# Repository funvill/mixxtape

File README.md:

# Mixxtape — a cassette you can actually record on

A 2-layer PCB in the form factor of a compact cassette (99.5 × 63.5 mm)
that slides into a real Norelco cassette case. The bare board **is** the object —
no enclosure, no bezel.

An onboard MEMS microphone records three 4-minute tracks. Hold REC to record,
release to stop. Pair it to any Bluetooth earbuds or speaker and press PLAY.

Cassette-shaped Bluetooth *players* exist. Nobody ships a cassette-shaped
**recorder** — and recording is the part that made a mixtape a mixtape.

![The Mixxtape board turning, front and back. The front carries the ESP32, two
rings of RGB LEDs around the routed-out reel windows, four buttons and a USB-C
port; the back is covered edge to edge in a peony line-art silkscreen.](artwork/mixxtape.gif)

<sub>3D render from KiCad. The mask reads green here because that is the
viewer's default — the board ships **matte white**, which is what makes the
sharpie label work.</sub>

![A cassette and its paper insert, both carrying the same black peony line-art
on an off-white ground, the insert showing a blank ruled label
box.](artwork/case-mockup.png)

<sub>Artwork mockup of the B-side design and the J-card insert. The board is
the object; this shows where the artwork is going.</sub>

## How you use it

- **Hold REC** — records. Release stops. Recording always overwrites the current
  track from zero — recording *is* erasing, same as tape.
- **PLAY** — plays all three tracks in order. It's a tape side, not three voice
  memos.
- **TRACK** — cycles track 1 → 2 → 3.
- **MODE (hold 2 s)** — pairing. Hold the board against your speaker; it picks
  the closest device by signal strength. No phone, no app, no list.
- Plug it in and it auto-reconnects to the last thing it paired with.

## Notable design features

- **Snap-off write-protect tab.** A mouse-bitten break-off PCB tab carries a
  trace to a GPIO. Snap it and the firmware refuses to record — permanently.
  Handing someone a tape becomes a ritual with a physical, irreversible step.
- **The reels show tape position.** Twelve RGB LEDs ring each routed-out reel
  window. During playback the left ring empties and the right ring fills, like
  tape transferring between reels. Red pulse tracks recording level.
- **Matte white solder mask** so you can sharpie the label on, with a ruled
  label block silkscreened where a cassette's paper label sits.
- **No battery.** USB-C only, and there is no charging circuit on the board
  at all. A cassette's promise is that you find it years later and it still
  works.
- **Jig-programmed.** No USB-UART on the board — USB-C is power only.
  Firmware loads through six pogo-pin pads via a programming jig.

## Hardware summary

Every fitted part is stocked at JLCPCB. The project rule is a minimum of 5,000
in stock, so a run never stalls on one line item — with a single documented
exception: **the microphone sits at ~3,500**, because no digital MEMS
microphone at JLCPCB clears the bar, and the one that does is analogue and
would wreck the audio path.

| Block | Part | JLCPCB | Qty | Notes |
|---|---|---|---|---|
| MCU | ESP32-WROOM-32E-N4 | [C701341](https://jlcpcb.com/partdetail/C701341) | 1 | The original Xtensa ESP32 — the only one with Classic Bluetooth, so the only one that can be an A2DP *source* |
| Microphone | MSM261DHT006 | [C51928215](https://jlcpcb.com/partdetail/C51928215) | 1 | **PDM** digital MEMS, mono, **top-ported** — sound enters from the component side, so there is no hole through the board |
| Storage | GD25Q128ESIG | [C2758105](https://jlcpcb.com/partdetail/C2758105) | 1 | 16 MB NOR flash, separate from the module's own flash. Three fixed slots, ~4 min each. Winbond W25Q128JVSIQ ([C97521](https://jlcpcb.com/partdetail/C97521)) is a drop-in second source |
| Indicators | XL-2020RGBC-2812B | [C5349954](https://jlcpcb.com/partdetail/C5349954) | 29 | WS2812-compatible RGB. Two 12-LED reel rings, three track lamps, REC, BT |
| LED data buffer | SN74AHCT1G125 | [C7484](https://jlcpcb.com/partdetail/C7484) | 1 | Lifts the ESP32's 3.3 V data line to the LEDs' 5 V rail |
| Regulator | AMS1117-3.3 | [C6186](https://jlcpcb.com/partdetail/C6186) | 1 | 5 V USB down to 3.3 V |
| USB-C | TYPE-C-31-M-12 | [C165948](https://jlcpcb.com/partdetail/C165948) | 1 | Power and CC sensing only — no data lines |
| Buttons | TS-1187A-B-A-B | [C318884](https://jlcpcb.com/partdetail/C318884) | 4 | REC, PLAY, TRACK, MODE |
| Write-protect tab | — | — | 1 | Not a part. A mouse-bitten PCB tongue carrying a net tie; snap it and recording is disabled for good |
| Programming pads | — | — | 1 | Six bare pogo targets. No USB-UART on the board |

Passives are all JLCPCB basic-library parts:
[10 µF 0805](https://jlcpcb.com/partdetail/C15850) ×2 (rail bulk),
[10 µF 0402](https://jlcpcb.com/partdetail/C15525),
[1 µF](https://jlcpcb.com/partdetail/C52923) (the ESP32's EN delay),
[100 nF](https://jlcpcb.com/partdetail/C1525) ×12,
[10 k](https://jlcpcb.com/partdetail/C25804) ×7,
[5.1 k](https://jlcpcb.com/partdetail/C25905) ×2 (the USB-C CC pull-downs) and
[100 Ω](https://jlcpcb.com/partdetail/C25076) (microphone supply isolation).

| | |
|---|---|
| Audio | 44.1 kHz mono, ADPCM-encoded at record time; playback decodes with table lookups and hands PCM to the Bluetooth stack |
| Power | USB-C only, power and CC sense. No battery, no charger |
| Board | 2-layer, 99.50 × 63.50 mm, matte white solder mask with black silkscreen |
| Cost | **$9.41/board** at a run of 20 — $173.14 in parts plus $15.00 of setup fees for five extended-library parts |

Full detail, with live stock and pricing, is in the
[generated BOM](docs/cassette-recorder-bom-v4.md) — it is derived from the
schematic, so it cannot drift out of step with it.

## Project status

**Design locked, schematic and firmware core underway.** `hardware/` holds a
KiCad 9 project with a first-pass schematic (ERC-clean) and JLCPCB part
libraries. `firmware/` has the ESP-IDF skeleton plus the host-tested core —
crash-safe slot manager, ADPCM codec, playback sequencer, reel display,
pairing policy, bond table and record limiter — all proven without hardware,
since there is no devkit. Target: a prototype run of 3–5 boards, then a full
run of 20. What is left needs a board in hand: the SPI flash, I²S capture,
the A2DP plumbing, LED output, and A2DP against real earbuds.

## Documentation

**Before ordering boards:**

- [Pre-production checklist](docs/PRE-PRODUCTION-CHECKLIST.md) — the
  case-fit test, open decisions, and what to re-quote
- [Case-fit test sheet](docs/case-fit-test-1to1.pdf) — print at 100%, cut
  out, put in a real cassette case

**For people using one:**

- [Cassette insert template](docs/jcard-template-1to1.pdf) — double-sided
  J-card for the case, 1:1, print at 100% ([side 1](docs/jcard-template-side1.svg), [side 2](docs/jcard-template-side2.svg))
- [Documentation index](docs/README.md) — everything below, organised
- [Quick-start pictograms](docs/quick-start-pictograms.html) — wordless
  instructions, one printable sheet
- [Manual](docs/MANUAL.md) — how to record, play, pair, and what the lights mean
- [FAQ](docs/FAQ.md) — including the honest limitations

**For people building or hacking one:**

- [Project write-up](docs/cassette-project-writeup.md) — the pitch, design
  rationale, and open questions
- [Agent handoff brief](docs/cassette-recorder-agent-brief.md) — the
  authoritative spec: locked decisions, GPIO map, behaviour spec, phase order
- [Bill of materials](docs/cassette-recorder-bom-v4.md) — generated from the
  schematic with live JLCPCB prices and stock, so it cannot drift
- [Line-out option](docs/line-out-option.md) — rejected; kept for the reasoning
  and the verified part numbers
- [Prior art](docs/prior-art.md) — research on cassette-form-factor projects
- [Firmware plan](docs/firmware-plan.md) — architecture, milestones, and
  hardware interface for the firmware agent

## Prior art

- **Mixtape Alpha** (Open Music Labs with Jie Qi / MIT Media Lab, 2012) — a
  cassette-shaped ATmega328p synth; the bare-PCB-as-object philosophy comes
  straight from it.
- **Mixxtape** (Mixxim) — the commercial cassette-shaped Bluetooth *player*.
  The thing this project is not.

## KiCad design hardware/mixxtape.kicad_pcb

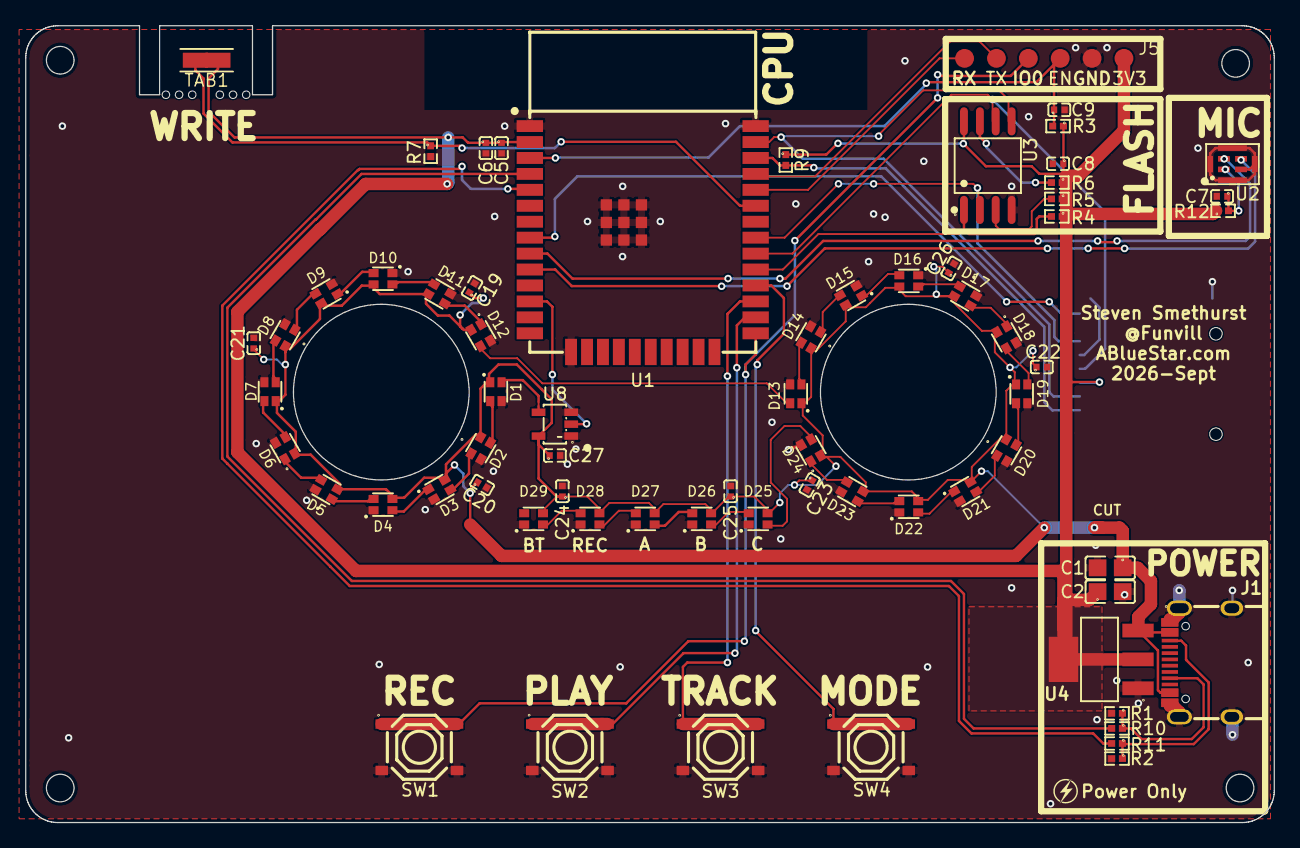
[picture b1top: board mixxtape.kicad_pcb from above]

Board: 2 copper layers, 99.5 x 63.5 mm, 70 parts (1 on the bottom side), 56 nets.

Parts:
C1, C2: 10uF; C0805
C5, C6, C7, C8, C19, C20, C21, C22, C23, C24, C25, C26, C27: C0402
C9: 1uF; C0402
D1, D2, D3, D4, D5, D6, D7, D8, D9, D10, D11, D12, D13, D14, D15, D16, D17, D18, D19, D20, D21, D22, D23, D24, D25, D26, D27, D28, D29: XL-1615RGBC-2812B; LED-SMD_4P-L1.6-W1.5_XL-1615RGBC-2812B
J1: USB-C_SMD-TYPE-C-31-M-12_1
J4: TF-SMD_TF-01A
J5: PROG_JIG; PROG_JIG_6PAD
MB1: MOUSEBITE_6
R1, R2: R0402
R3, R4, R5, R6, R7, R9, R10, R11: R0603; R0402
R12: 100R; R0402
SW1, SW2, SW3, SW4: SW-SMD_4P-L5.1-W5.1-P3.70-LS6.5-TL_H1.5
TAB1: WRITE-PROTECT; TAB_BREAKOFF_LINK
U1: WIFI-SMD_ESP32-WROOM-32E
U2: LGA-8_L4.0-W3.0-R_WMM7040DT0
U3: SOIC-8_L5.3-W5.3-P1.27-LS8.0-BL
U4: SOT-223-3_L6.5-W3.4-P2.30-LS7.0-BR
U8: SOT-23-5_L3.0-W1.7-P0.95-LS2.8-BR

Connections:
3V3: C2.1, C5.1, C6.1, C8.1, J4.4, J5.1, R3.1, R4.1, R5.1, R6.1, R9.1, R12.1, TAB1.1, U1.2, U3.8, U4.2, U4.4
BTN_MODE: SW4.1, SW4.2, U1.28
BTN_PLAY: SW2.1, SW2.2, U1.26
BTN_REC: J5.4, SW1.1, SW1.2, U1.25
BTN_TRACK: SW3.1, SW3.2, U1.27
CC1: J1.A5, R1.1, R10.1
CC1_SENSE: R10.2, U1.4
CC2: J1.B5, R2.1, R11.1
CC2_SENSE: R11.2, U1.5
EN: C9.1, J5.3, R3.2, U1.3
FLASH_HOLD_N: R6.2, U3.7
FLASH_WP_N: R5.2, U3.3
GND: C1.2, C2.2, C5.2, C6.2, C7.2, C8.2, C9.2, C19.2, C20.2, C21.2, C22.2, C23.2, C24.2, C25.2, C26.2, C27.2, D1.1, D2.1, D3.1, D4.1, D5.1, D6.1, D7.1, D8.1, D9.1, D10.1, D11.1, D12.1, D13.1, D14.1, D15.1, D16.1, D17.1, D18.1, D19.1, D20.1, D21.1, D22.1, D23.1, D24.1, D25.1, D26.1, D27.1, D28.1, D29.1, J1.1, J1.2, J1.3, J1.4, J1.A1B12, J1.B1A12, J4.6, J4.10, J4.11, J4.12, J4.13, J5.2, R1.2, R2.2, R7.2, SW1.3, SW1.4, SW2.3, SW2.4, SW3.3, SW3.4, SW4.3, SW4.4, U1.1, U1.15, U1.38, U1.39, U2.2, U2.5, U2.6, U2.7, U2.8, U3.4, U4.1, U8.1, U8.3
LD1: D1.4, D2.2
LD2: D2.4, D3.2
LD3: D3.4, D4.2
LD4: D4.4, D5.2
LD5: D5.4, D6.2
LD6: D6.4, D7.2
LD7: D7.4, D8.2
LD8: D8.4, D9.2
LD9: D9.4, D10.2
LD10: D10.4, D11.2
LD11: D11.4, D12.2
LD12: D12.4, D13.2
LD13: D13.4, D14.2
LD14: D14.4, D15.2
LD15: D15.4, D16.2
LD16: D16.4, D17.2
LD17: D17.4, D18.2
LD18: D18.4, D19.2
LD19: D19.4, D20.2
LD20: D20.4, D21.2
LD21: D21.4, D22.2
LD22: D22.4, D23.2
LD23: D23.4, D24.2
LD24: D24.4, D25.2
LD25: D25.4, D26.2
LD26: D26.4, D27.2
LD27: D27.4, D28.2
LD28: D28.4, D29.2
LED_DATA: U1.12, U8.2
LED_DATA_5V: D1.2, U8.4
MIC_VDD: C7.1, R12.2, U2.1
PDM_CLK: U1.10, U2.3
PDM_DATA: U1.9, U2.4
SD_CS_N: J4.2, R9.2, U1.36
SD_DETECT: J4.9, U1.8
SPI_CLK: J4.5, U1.30, U3.6
SPI_CS_N: R4.2, U1.29, U3.1
SPI_MISO: J4.7, U1.31, U3.2
SPI_MOSI: J4.3, U1.37, U3.5
TAB_SENSE: R7.1, TAB1.2, U1.33
UART_RX: J5.6, U1.34
UART_TX: J5.5, U1.35
VBUS: C1.1, C19.1, C20.1, C21.1, C22.1, C23.1, C24.1, C25.1, C26.1, C27.1, D1.3, D2.3, D3.3, D4.3, D5.3, D6.3, D7.3, D8.3, D9.3, D10.3, D11.3, D12.3, D13.3, D14.3, D15.3, D16.3, D17.3, D18.3, D19.3, D20.3, D21.3, D22.3, D23.3, D24.3, D25.3, D26.3, D27.3, D28.3, D29.3, J1.A4B9, J1.B4A9, U4.3, U8.5

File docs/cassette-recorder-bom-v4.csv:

Comment,Designator,Footprint,JLCPCB Part #
"22uF","C1 C2","C0805","C45783"
"10uF","C5","C0402","C15525"
"100nF","C6 C7 C8 C19 C20 C21 C22 C23 C24 C25 C26 C27","C0402","C1525"
"1uF","C9","C0402","C29266"
"WS2812B-2020","D1 D2 D3 D4 D5 D6 D7 D8 D9 D10 D11 D12 D13 D14 D15 D16 D17 D18 D19 D20 D21 D22 D23 D24 D25 D26 D27 D28 D29","LED-SMD_4P-L2.0-W2.0-TL_WS2812B-2020","C5349955"
"USB-C-16P","J1","USB-C_SMD-TYPE-C-31-M-12_1","C165948"
"5.1k","R1 R2","R0402","C25905"
"10k","R3 R4 R5 R6 R7 R10 R11","R0603","C25804"
"100R","R12","R0402","C25076"
"PLAY / TRACK / MODE / REC","SW1 SW2 SW3 SW4","SW-SMD_4P-L5.1-W5.1-P3.70-LS6.5-TL_H1.5","C318884"
"ESP32-WROOM-32E-N4","U1","WIFI-SMD_ESP32-WROOM-32E","C701341"
"MSM261DHT006","U2","LGA-8_L4.0-W3.0-R_WMM7040DT0","C51928215"
"W25Q128JVSIQ","U3","SOIC-8_L5.3-W5.3-P1.27-LS8.0-BL","C97521"
"AMS1117-3.3","U4","SOT-223-3_L6.5-W3.4-P2.30-LS7.0-BR","C6186"
"SN74AHCT1G125","U8","SOT-23-5_L3.0-W1.7-P0.95-LS2.8-BR","C7484"

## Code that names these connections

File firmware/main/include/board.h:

/* Pin map for the rev 0.1 board.
 *
 * Authoritative source: docs/firmware-plan.md sec.2, which supersedes the
 * GPIO table in docs/cassette-recorder-agent-brief.md sec.5 (USB-C is now
 * power-only, programming is via the J5 pogo pads, and SENSOR_VP/VN sense
 * the USB-C CC lines).
 *
 * ESP32 constraints honoured here:
 *   GPIO 6-11  are the module's own flash — never used
 *   GPIO 12    is the MTDI strap and must be low at boot — left unused
 *   GPIO 34/35/36/39 are input-only
 */
#ifndef BOARD_H
#define BOARD_H

#include "tape_layout.h" /* TAPE_SAMPLE_RATE */

/* --- PDM microphone (MSM261DHT006, mono, L/R tied low) --------------
 * PDM rather than I2S: two wires instead of three, so the old bit-clock
 * pin (GPIO26) is now free. The ESP32's I2S peripheral does PDM receive
 * in hardware, decimating to PCM on the way in, so nothing downstream
 * changes.
 *
 * Clock rate matters here. PDM clock = sample rate x downsample ratio:
 *   44100 x 64  = 2.8224 MHz  -> inside the mic's 1.1-4.8 MHz window
 *   44100 x 128 = 5.6448 MHz  -> ABOVE its 4.8 MHz maximum
 * so the downsample ratio must be 64. Picking 128 would run the part out
 * of spec and is the obvious mistake to make here.
 *
 * The part is TOP-ported: sound enters from the component side, and there
 * is deliberately no hole through the board beneath it. Keep its top face
 * clear of case ribs, labels and fingers.
 */
#define PIN_PDM_CLK  25 /* ESP32 -> mic, 2.8224 MHz */
#define PIN_PDM_DATA 33 /* mic -> ESP32            */

#define PDM_DOWNSAMPLE_RATIO 64
#define PDM_CLOCK_HZ         (TAPE_SAMPLE_RATE * PDM_DOWNSAMPLE_RATIO)

/* --- VSPI: audio flash (W25Q128) + optional microSD (DNP) ----------- */
#define PIN_SPI_SCK   18
#define PIN_SPI_MISO  19
#define PIN_SPI_MOSI  23
#define PIN_FLASH_CS   5
#define PIN_SD_CS     22 /* microSD is DNP on the default build         */
#define PIN_SD_DETECT 32 /* switch to GND; needs an internal pull-up    */

/* --- WS2812 chain (via SN74AHCT1G125 level shifter) ----------------- */
#define PIN_LED_DATA 27
#define LED_COUNT    29
#define LED_REEL_LEFT_FIRST   0  /* D1-D12  */
#define LED_REEL_LEFT_COUNT   12
#define LED_REEL_RIGHT_FIRST  12 /* D13-D24 */
#define LED_REEL_RIGHT_COUNT  12
#define LED_TRACK_FIRST       24 /* D25-D27 */
#define LED_TRACK_COUNT       3
#define LED_REC               27 /* D28 */
#define LED_BT                28 /* D29 */

/* Global brightness ceiling. All 29 LEDs at full white is ~1.7 A; the
 * default USB-C budget is 500 mA until CC sensing says otherwise. */
/* Re-derived 2026-08-30 against the real part. At 5 mA/channel all 29 LEDs
 * at full white draw about 435 mA, not the 1.7 A the old caps assumed.
 *
 *   Default USB (500 mA guaranteed): an ESP32 Bluetooth TX burst takes
 *   ~250 mA through the linear regulator, leaving ~250 mA for the array.
 *   130/255 gives 435 * 130/255 = 222 mA, for ~472 mA total.
 *
 *   A 1.5 A source can supply the whole array at full, so the cap there is
 *   the part's own limit rather than the supply's.
 *
 * Firmware MUST read CC1_SENSE/CC2_SENSE before using the HIGH cap - the
 * board advertises itself as a plain sink (5.1k Rd), so a host is only
 * obliged to give 500 mA. */
#define LED_BRIGHTNESS_USB_DEFAULT 130 /* /255, ~51%, ~222 mA of array */
#define LED_BRIGHTNESS_USB_HIGH    255 /* /255, full, ~435 mA of array  */

/* --- Buttons: active low, internal pull-ups -------------------------- */
#define PIN_BTN_REC   0  /* also the BOOT strap — safe as active-low     */
#define PIN_BTN_PLAY  4
#define PIN_BTN_TRACK 16
#define PIN_BTN_MODE  17

/* --- Write-protect tab: external 10k pull-down, intact = high -------- */
#define PIN_TAB_SENSE 21

/* --- USB-C CC sense (ADC1) ------------------------------------------ */
#define PIN_CC1_SENSE 36 /* SENSOR_VP */
#define PIN_CC2_SENSE 39 /* SENSOR_VN */

/* CC voltage thresholds in millivolts, at the divider we fit (Rd = 5.1k,
 * sensed through 10k). Source advertises: ~0.41 V default (500 mA),
 * ~0.92 V (1.5 A), ~1.68 V (3 A). Thresholds sit mid-band. */
#define CC_MV_THRESHOLD_1A5 660
#define CC_MV_THRESHOLD_3A0 1230

/* --- UART to the programming jig (J5 pogo pads) ---------------------- */
#define PIN_UART_TX 1
#define PIN_UART_RX 3

/* --- Unpopulated (DNP) ---------------------------------------------- */
#define PIN_BATT_SENSE 34 /* divider not fitted  */
#define PIN_LINE_IN    35 /* jack not fitted     */

#endif /* BOARD_H */
